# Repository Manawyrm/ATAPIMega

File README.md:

ATAPIMega
=============================

### Overview

[ATAPIMega](https://github.com/Manawyrm/ATAPIMega) is a hardware project which allows regular (P)ATA CD/DVD drives to be used as a standalone Audio-CD player.  
This repository contains KiCAD PCB design and schematic for the CD player.  

The PCB accepts (regulated!) 12V DC power via a 5.5mm/2.1mm barrel jack and outputs 12V/5V for the CD drive.  
The microcontroller is an ATmega2560 (Arduino Mega-compatible), chosen for 5V-I/O voltage and high pin-count (and bad availability of STM32's in the component shortage of 2021).

### Manufacturing
The PCB can be fully assembled at [JLCPCBs](https://jlcpcb.com/DDE) assembly service, including through-hole parts. Only the LCD will have to be installed manually.
Manufacturing files for automatic assembly service can be found at `gerbers/RevA/ATAPIMega/`.  

Due to the high amount of extended components, setup fees are quite high (~30$).  
Price will decrease significantly with higher board count (~15$/board).

### Additional info 

[Schematic](gerbers/RevA/ATAPIMega/ATAPIMega.pdf)  
[Interactive BOM](https://tbspace.de/content/downloads/atapimega-ibom-reva.html)  
[Firmware](https://github.com/Manawyrm/ATAPIMega-Firmware)  

### Errata
Rev.A: FTDI / UART connector reset circuitry is wrong, needs bodge resistor!

### Future improvements
- mounting holes
- labeling of audio ports (LGGR, etc.)
- power switch

### Credits
5V Step-Down switch-mode regulator was designed with a lot of help from [@Toble_Miner](https://github.com/TobleMiner)! Thanks!

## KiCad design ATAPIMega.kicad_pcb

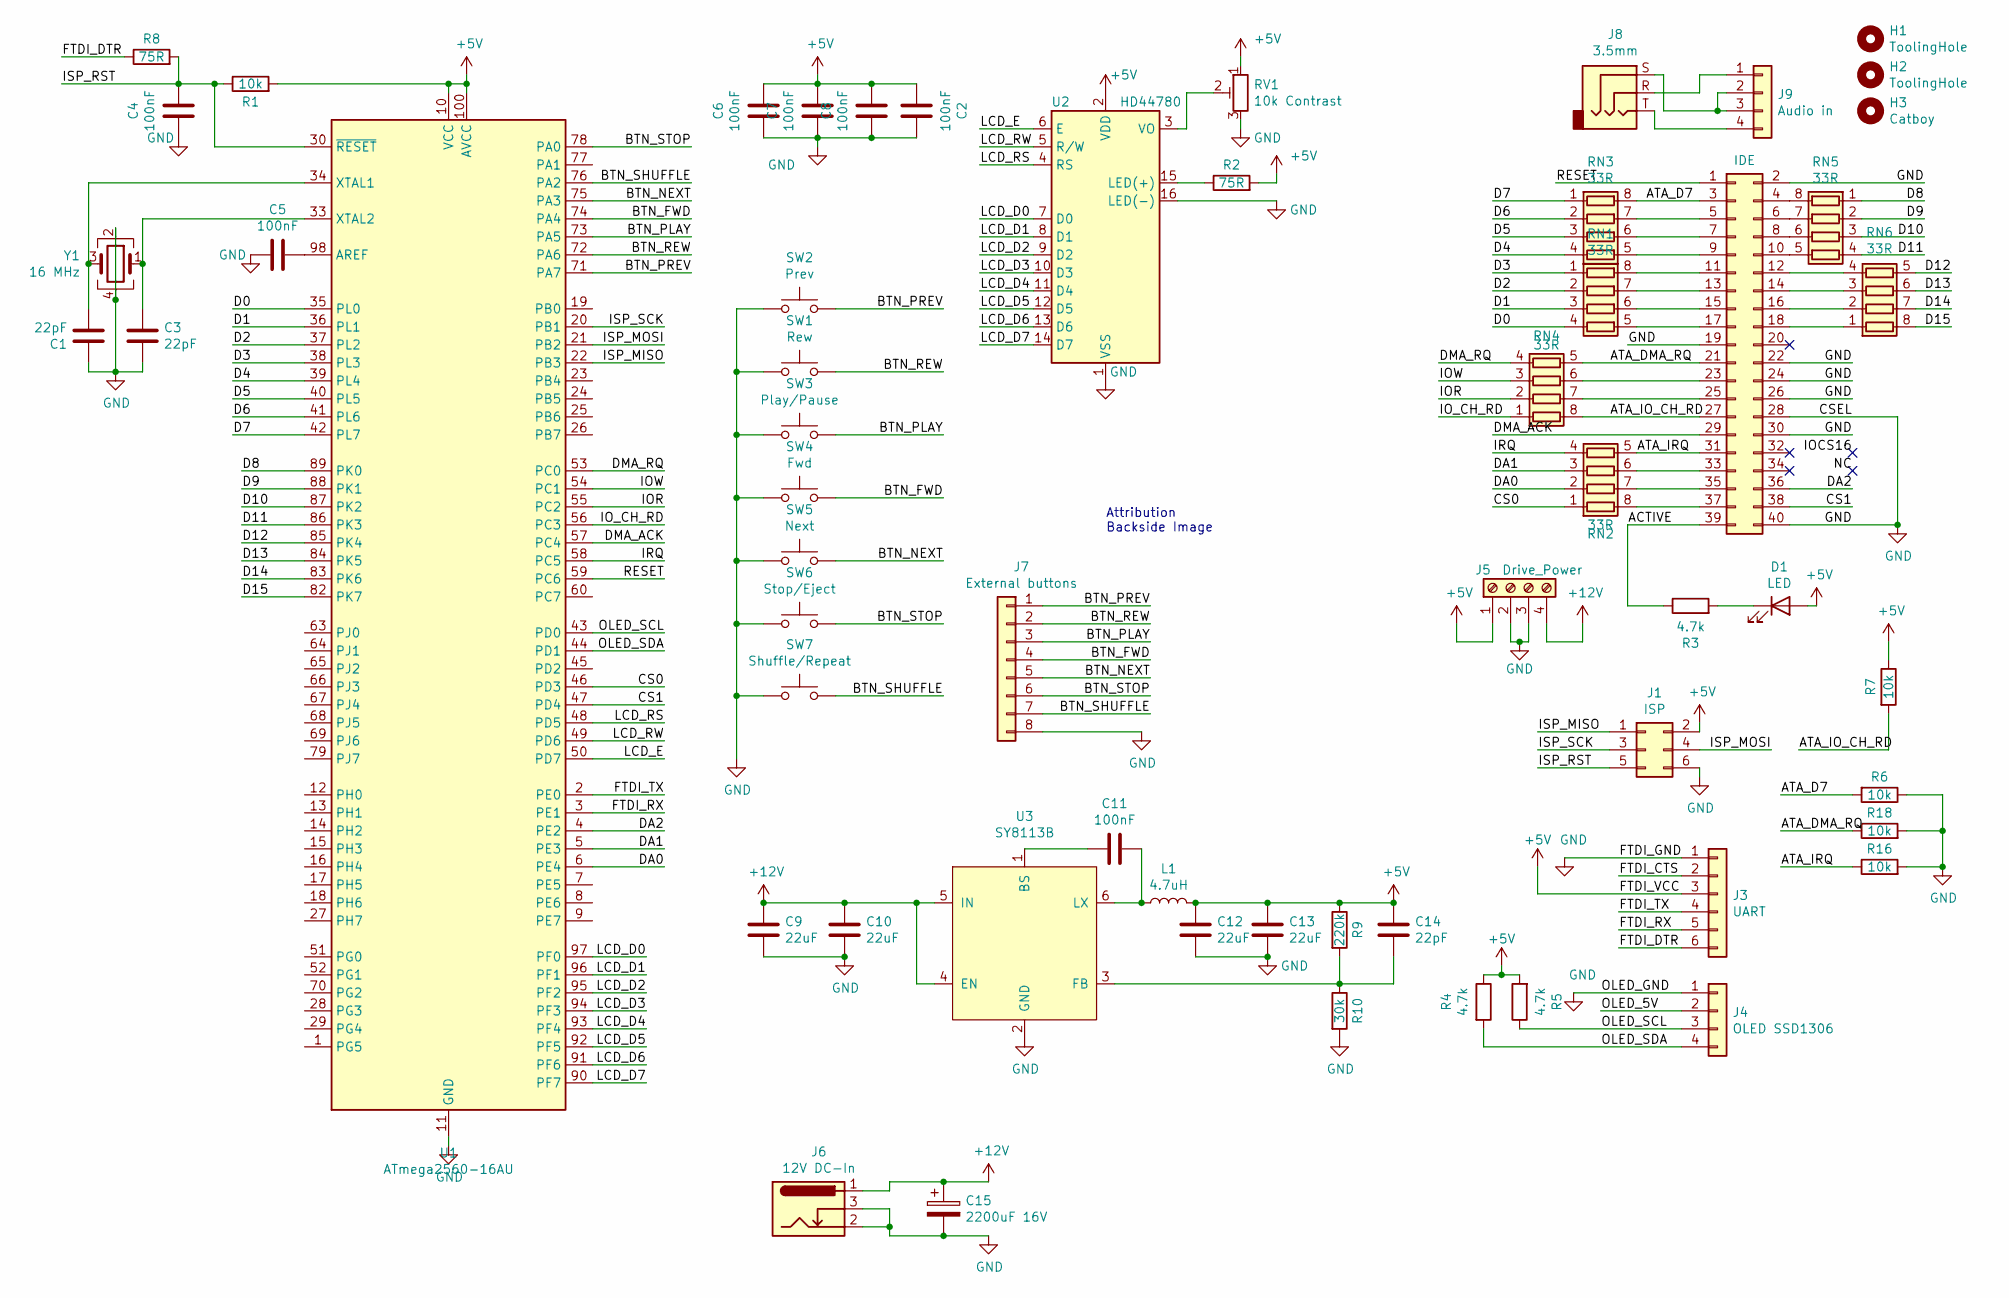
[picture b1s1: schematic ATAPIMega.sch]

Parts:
C1, C3, C14: 22pF; C_0402_1005Metric; LCSC C1555
C2, C4, C5, C6, C7, C8, C11: 100nF; C_0402_1005Metric; LCSC C1525
C9, C10, C12, C13: 22uF; C_0805_2012Metric; LCSC C45783
C15: 2200uF 16V; CP_Radial_D13.0mm_P5.00mm; LCSC C88768
D1: LED; LED_0603_1608Metric; LCSC C72043
H1, H2: ToolingHole; ToolingHole_JLCSMT
H3: Catboy; catboy
J1: ISP; IDC-Header_2x03_P2.54mm_Vertical; LCSC C11214
J2: IDE; IDC-Header_2x20_P2.54mm_Vertical; LCSC C9138
J3: UART; PinHeader_1x06_P2.54mm_Vertical; LCSC C37208
J4: OLED SSD1306; PinHeader_1x04_P2.54mm_Vertical
J5: Drive_Power; TerminalBlock_RND_205-00003_1x04_P5.00mm_Horizontal; LCSC C192779
J6: 12V DC-In; BarrelJack_DC-005-2.0_C16214; LCSC C16214
J7: External buttons; PinHeader_1x08_P2.54mm_Vertical
J8: 3.5mm; Jack_3.5mm_CUI_SJ1-3535NG_Horizontal; LCSC C26230
J9: Audio in; PinHeader_1x04_P2.54mm_Vertical; LCSC C492403
L1: 4.7uH; L_Bourns_SRP7028A_7.3x6.6mm; LCSC C207840
R1, R6, R7, R16, R18: 10k; R_0402_1005Metric; LCSC C25744
R2, R8: 75R; R_0402_1005Metric; LCSC C25133
R3, R4, R5: 4.7k; R_0402_1005Metric; LCSC C25900
R9: 220k; R_0603_1608Metric; LCSC C22961
R10: 30k; R_0603_1608Metric; LCSC C22984
RN1, RN2, RN3, RN4, RN5, RN6: 33R; R_Array_Convex_4x0402; LCSC C25501
RV1: 10k Contrast; Potentiometer_Bourns_3296W_Vertical; LCSC C118954
SW1: Rew; SW_Push_1P1T_NO_6x6mm_H9.5mm; LCSC C381038
SW2: Prev; SW_Push_1P1T_NO_6x6mm_H9.5mm; LCSC C381038
SW3: Play/Pause; SW_Push_1P1T_NO_6x6mm_H9.5mm; LCSC C381038
SW4: Fwd; SW_Push_1P1T_NO_6x6mm_H9.5mm; LCSC C381038
SW5: Next; SW_Push_1P1T_NO_6x6mm_H9.5mm; LCSC C381038
SW6: Stop/Eject; SW_Push_1P1T_NO_6x6mm_H9.5mm; LCSC C381038
SW7: Shuffle/Repeat; SW_Push_1P1T_NO_6x6mm_H9.5mm; LCSC C381038
U1: ATmega2560-16AU; TQFP-100_14x14mm_P0.5mm; LCSC C22460
U2: HD44780; WC1602A
U3: SY8113B; TSOT-23-6; LCSC C78989
Y1: 16 MHz; Crystal_SMD_3225-4Pin_3.2x2.5mm; LCSC C13738

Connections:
+5V: C2.2, C6.1, C7.1, C8.1, C12.1, C13.1, C14.1, D1.2 (A), J1.2, J3.3, J5.1, L1.2, R1.2, R2.2, R4.1, R5.2, R7.1, R9.1, RV1.1, U1.10 (VCC), U1.31 (VCC), U1.61 (VCC), U1.80 (VCC), U1.100 (AVCC), U2.2 (VDD)
+12V: C9.1, C10.1, C15.1, J5.4, J6.1, U3.4 (EN), U3.5 (IN)
/ACTIVE: J2.39, R3.1
/ATA_D7: J2.3, R6.2, RN3.8 (R1.2)
/ATA_DMA_RQ: J2.21, R18.1, RN4.5 (R4.2)
/ATA_IO_CH_RD: J2.27, R7.2, RN4.8 (R1.2)
/ATA_IRQ: J2.31, R16.1, RN2.5 (R4.2)
/BTN_FWD: J7.4, SW4.2, U1.74 (PA4)
/BTN_NEXT: J7.5, SW5.2, U1.75 (PA3)
/BTN_PLAY: J7.3, SW3.2, U1.73 (PA5)
/BTN_PREV: J7.1, SW2.2, U1.71 (PA7)
/BTN_REW: J7.2, SW1.2, U1.72 (PA6)
/BTN_SHUFFLE: J7.7, SW7.2, U1.76 (PA2)
/BTN_STOP: J7.6, SW6.2, U1.78 (PA0)
/CS0: RN2.1 (R1.1), U1.46 (PD3)
/CS1: J2.38, U1.47 (PD4)
/D0: RN1.4 (R4.1), U1.35 (PL0)
/D1: RN1.3 (R3.1), U1.36 (PL1)
/D2: RN1.2 (R2.1), U1.37 (PL2)
/D3: RN1.1 (R1.1), U1.38 (PL3)
/D4: RN3.4 (R4.1), U1.39 (PL4)
/D5: RN3.3 (R3.1), U1.40 (PL5)
/D6: RN3.2 (R2.1), U1.41 (PL6)
/D7: RN3.1 (R1.1), U1.42 (PL7)
/D8: RN5.1 (R1.1), U1.89 (PK0)
/D9: RN5.2 (R2.1), U1.88 (PK1)
/D10: RN5.3 (R3.1), U1.87 (PK2)
/D11: RN5.4 (R4.1), U1.86 (PK3)
/D12: RN6.5 (R4.2), U1.85 (PK4)
/D13: RN6.6 (R3.2), U1.84 (PK5)
/D14: RN6.7 (R2.2), U1.83 (PK6)
/D15: RN6.8 (R1.2), U1.82 (PK7)
/DA0: RN2.2 (R2.1), U1.6 (PE4)
/DA1: RN2.3 (R3.1), U1.5 (PE3)
/DA2: J2.36, U1.4 (PE2)
/DMA_ACK: J2.29, U1.57 (PC4)
/DMA_RQ: RN4.4 (R4.1), U1.53 (PC0)
/FTDI_CTS: J3.2
/FTDI_DTR: J3.6, R8.1
/FTDI_RX: J3.5, U1.3 (PE1)
/FTDI_TX: J3.4, U1.2 (PE0)
/IOR: RN4.2 (R2.1), U1.55 (PC2)
/IOW: RN4.3 (R3.1), U1.54 (PC1)
/IO_CH_RD: RN4.1 (R1.1), U1.56 (PC3)
/IRQ: RN2.4 (R4.1), U1.58 (PC5)
/ISP_MISO: J1.1, U1.22 (PB3)
/ISP_MOSI: J1.4, U1.21 (PB2)
/ISP_RST: C4.1, J1.5, R1.1, R8.2, U1.30 (~RESET)
/ISP_SCK: J1.3, U1.20 (PB1)
/LCD_D0: U1.97 (PF0), U2.7 (D0)
/LCD_D1: U1.96 (PF1), U2.8 (D1)
/LCD_D2: U1.95 (PF2), U2.9 (D2)
/LCD_D3: U1.94 (PF3), U2.10 (D3)
/LCD_D4: U1.93 (PF4), U2.11 (D4)
/LCD_D5: U1.92 (PF5), U2.12 (D5)
/LCD_D6: U1.91 (PF6), U2.13 (D6)
/LCD_D7: U1.90 (PF7), U2.14 (D7)
/LCD_E: U1.50 (PD7), U2.6 (E)
/LCD_RS: U1.48 (PD5), U2.4 (RS)
/LCD_RW: U1.49 (PD6), U2.5 (R/W)
/OLED_5V: J4.2
/OLED_SCL: J4.3, R5.1, U1.43 (PD0)
/OLED_SDA: J4.4, R4.2, U1.44 (PD1)
/RESET: J2.1, U1.59 (PC6)
GND: C1.1, C2.1, C3.2, C4.2, C5.2, C6.2, C7.2, C8.2, C9.2, C10.2, C12.2, C13.2, C15.2, J1.6, J2.2, J2.19, J2.22, J2.24, J2.26, J2.28, J2.30, J2.40, J3.1, J4.1, J5.2, J5.3, J6.2, J6.3, J7.8, R6.1, R10.2, R16.2, R18.2, RV1.3, SW1.1, SW2.1, SW3.1, SW4.1, SW5.1, SW6.1, SW7.1, U1.11 (GND), U1.32 (GND), U1.62 (GND), U1.81 (GND), U1.99 (GND), U2.1 (VSS), U2.16 (LED(-)), U3.2 (GND), Y1.2, Y1.4
unnamed: C1.2, U1.34 (XTAL1), Y1.3
unnamed: C3.1, U1.33 (XTAL2), Y1.1
unnamed: C5.1, U1.98 (AREF)
unnamed: C11.1, L1.1, U3.6 (LX)
unnamed: C11.2, U3.1 (BS)
unnamed: C14.2, R9.2, R10.1, U3.3 (FB)
unnamed: D1.1 (K), R3.2
unnamed: J2.4, RN5.8 (R1.2)
unnamed: J2.5, RN3.7 (R2.2)
unnamed: J2.6, RN5.7 (R2.2)
unnamed: J2.7, RN3.6 (R3.2)
unnamed: J2.8, RN5.6 (R3.2)
unnamed: J2.9, RN3.5 (R4.2)
unnamed: J2.10, RN5.5 (R4.2)
unnamed: J2.11, RN1.8 (R1.2)
unnamed: J2.12, RN6.4 (R4.1)
unnamed: J2.13, RN1.7 (R2.2)
unnamed: J2.14, RN6.3 (R3.1)
unnamed: J2.15, RN1.6 (R3.2)
unnamed: J2.16, RN6.2 (R2.1)
unnamed: J2.17, RN1.5 (R4.2)
unnamed: J2.18, RN6.1 (R1.1)
unnamed: J2.23, RN4.6 (R3.2)
unnamed: J2.25, RN4.7 (R2.2)
unnamed: J2.33, RN2.6 (R3.2)
unnamed: J2.35, RN2.7 (R2.2)
unnamed: J2.37, RN2.8 (R1.2)
unnamed: J8.R, J9.1
unnamed: J8.S, J9.2, J9.3
unnamed: J8.T, J9.4
unnamed: R2.1, U2.15 (LED(+))
unnamed: RV1.2, U2.3 (VO)

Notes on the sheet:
Attribution Backside Image

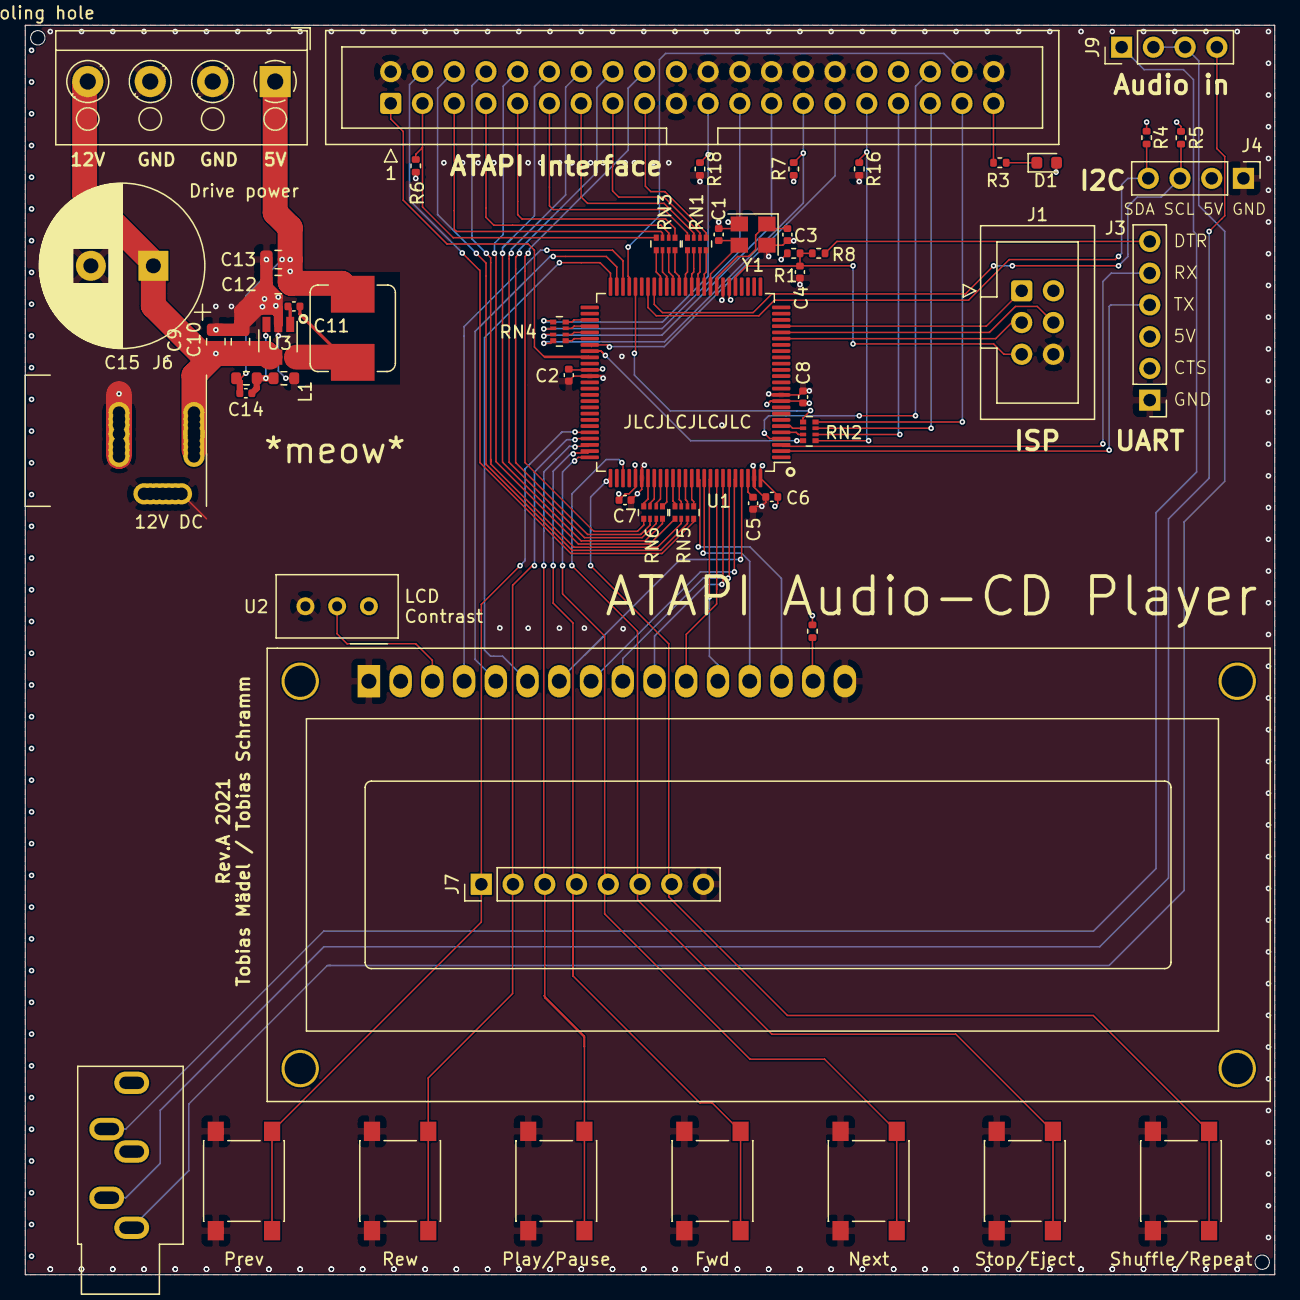
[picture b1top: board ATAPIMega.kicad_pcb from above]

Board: 4 copper layers, 100.0 x 100.0 mm, 59 parts (1 on the bottom side), 95 nets.

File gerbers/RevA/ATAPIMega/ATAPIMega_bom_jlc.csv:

"Comment","Designator","Footprint","LCSC Part #"
"100nF","C5,C4,C6,C7,C8,C11,C2","C_0402_1005Metric","C1525"
"22uF","C10,C9,C13,C12","C_0805_2012Metric","C45783"
"22pF","C14,C1,C3","C_0402_1005Metric","C1555"
"2200uF 16V","C15","CP_Radial_D13.0mm_P5.00mm","C88768"
"LED","D1","LED_0603_1608Metric","C72043"
"ISP","J1","IDC-Header_2x03_P2.54mm_Vertical","C11214"
"IDE","J2","IDC-Header_2x20_P2.54mm_Vertical","C9138"
"UART","J3","PinHeader_1x06_P2.54mm_Vertical","C37208"
"Drive_Power","J5","TerminalBlock_RND_205-00003_1x04_P5.00mm_Horizontal","C192779"
"12V DC-In","J6","BarrelJack_DC-005-2.0_C16214","C16214"
"3.5mm","J8","Jack_3.5mm_CUI_SJ1-3535NG_Horizontal","C26230"
"Audio in","J9","PinHeader_1x04_P2.54mm_Vertical","C492403"
"4.7uH","L1","L_Bourns_SRP7028A_7.3x6.6mm","C207840"
"75R","R2,R8","R_0402_1005Metric","C25133"
"4.7k","R3,R5,R4","R_0402_1005Metric","C25900"
"220k","R9","R_0603_1608Metric","C22961"
"30k","R10","R_0603_1608Metric","C22984"
"10k","R16,R18,R6,R7,R1","R_0402_1005Metric","C25744"
"33R","RN3,RN1,RN4,RN2,RN6,RN5","R_Array_Convex_4x0402","C25501"
"10k Contrast","RV1","Potentiometer_Bourns_3296W_Vertical","C118954"
"Rew","SW1","SW_Push_1P1T_NO_6x6mm_H9.5mm","C381038"
"Prev","SW2","SW_Push_1P1T_NO_6x6mm_H9.5mm","C381038"
"Play/Pause","SW3","SW_Push_1P1T_NO_6x6mm_H9.5mm","C381038"
"Fwd","SW4","SW_Push_1P1T_NO_6x6mm_H9.5mm","C381038"
"Next","SW5","SW_Push_1P1T_NO_6x6mm_H9.5mm","C381038"
"Stop/Eject","SW6","SW_Push_1P1T_NO_6x6mm_H9.5mm","C381038"
"Shuffle/Repeat","SW7","SW_Push_1P1T_NO_6x6mm_H9.5mm","C381038"
"ATmega2560-16AU","U1","TQFP-100_14x14mm_P0.5mm","C22460"
"SY8113B","U3","TSOT-23-6","C78989"
"16 MHz","Y1","Crystal_SMD_3225-4Pin_3.2x2.5mm","C13738"

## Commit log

2021-08-07 Add PCB
2021-08-08 RevA
